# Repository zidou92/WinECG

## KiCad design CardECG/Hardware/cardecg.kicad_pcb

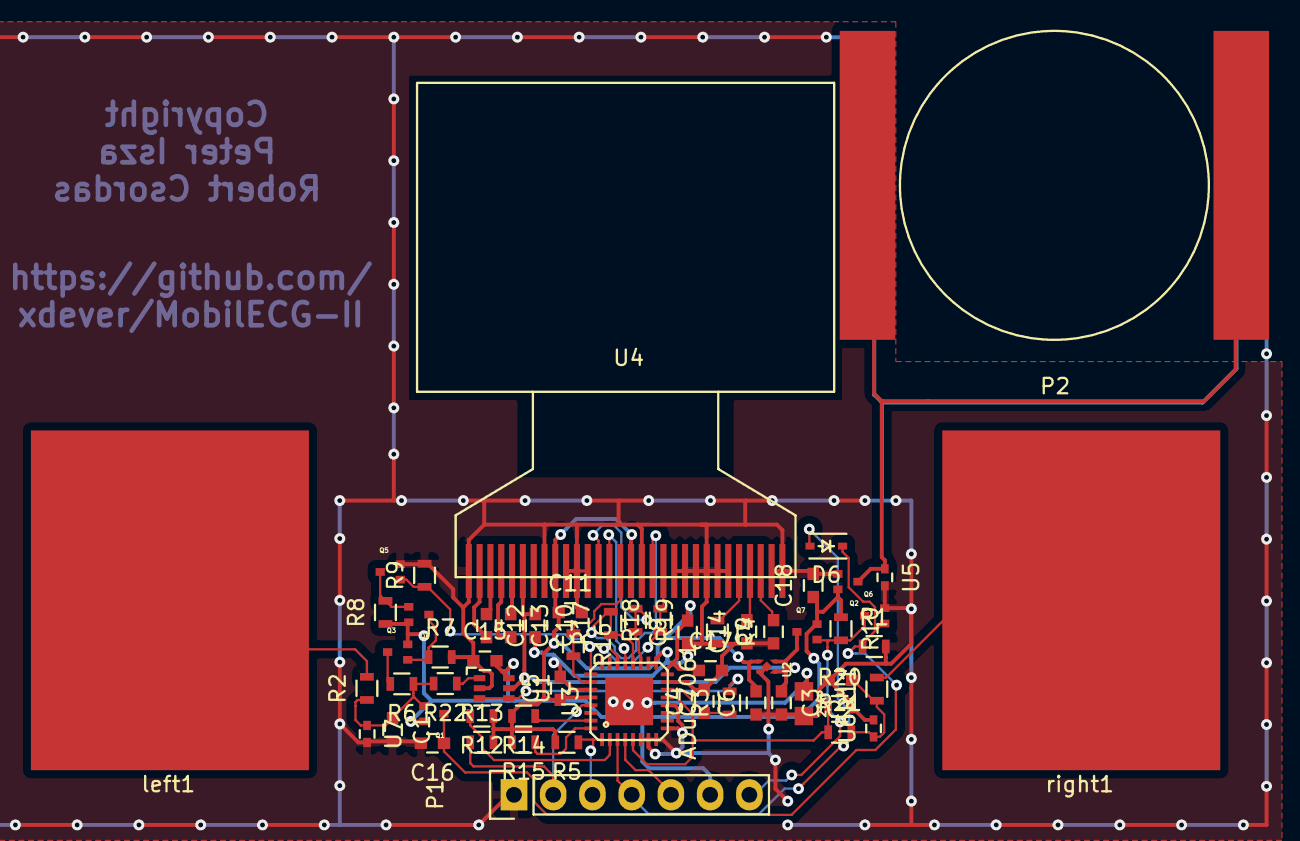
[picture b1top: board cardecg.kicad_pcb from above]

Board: 2 copper layers, 59 parts (0 on the bottom side), 39 nets.

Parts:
C1: 100pF; C_0603
C2, C5, C8, C15, C16: 100nF; C_0603
C3, C6, C10, C11, C12, C13, C17, C18: 1uF; C_0603
C4: 8.2nF NP0; C_0603
C9: 2.2uF; C_0603
C14: 4.7uF 16V; C_0603
CN1: 2TAP
D6: D; SOD-323
P1: PROG; Pin_Header_Straight_1x07
P2: BATTERY; CR2016
Q1, Q2, Q3, Q4, Q7: NX3008PBKT; SOT416
Q5, Q6: NX3008NBKT; SOT416
R1, R2, R3, R5, R8, R9, R10, R11, R12, R14, R15, R20: 47k; R_0603
R4: 390k; R_0603
R6, R7: 10M; R_0603
R13, R21, R22: 3.9k; R_0603
R16, R17, R18, R19: 49; R_0603
U1: LMV341; SC-70-6
U2: LD6805K/25; DFN1010C-4
U3: ADuC7061; LFCSP_VQ_CP32-2
U4: SSD1306
U5, U6, U7: TPD1E10B06; C_0402
left1: CONN_1; ecgpad
right1: CONN_1; ecgpad

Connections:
+BATT: C15.2, C18.1, P1.6, Q1.2, Q2.2, Q3.2, Q4.2, Q7.2, R8.1, R10.1, U1.6
GND: C1.2, C2.2, C3.2, C4.2, C5.2, C6.1, C8.1, C9.1, C10.2, C11.2, C14.1, C15.1, C16.2, C17.2, C18.2, CN1.2, P1.1, P2.3, P2.4, Q2.1, Q5.2, Q6.2, R1.2, R4.2, R7.2, R9.2, R20.2, U1.2, U2.2, U2.PAD, U3.6, U3.7, U3.8, U3.9, U3.12, U3.15, U3.17, U3.18, U3.27, U4.1, U4.8, U4.10, U4.11, U4.12, U4.17, U4.20, U4.21, U4.22, U4.23, U4.24, U4.25, U4.29, U4.30, U5.2, U6.2, U7.2
unnamed: C1.1, Q1.1, R2.1, R6.1, R22.2, U7.1
unnamed: C2.1, R11.1, R21.2, U6.1
unnamed: C4.1, R3.1, U3.14
unnamed: C9.2, U4.28
unnamed: C12.1, U4.3
unnamed: C12.2, U4.2
unnamed: C13.1, U4.5
unnamed: C13.2, U4.4
unnamed: C14.2, U4.27
unnamed: C16.1, D6.1, Q1.3, Q6.1, R1.1
unnamed: CN1.1, U3.33
unnamed: P2.1, P2.2, Q2.3, U5.1
unnamed: Q3.1, Q4.3, R7.1
unnamed: Q3.3, R6.2
unnamed: Q4.1, Q5.3, R8.2
unnamed: R2.2, left1.1
unnamed: R3.2, U1.3, U1.4
unnamed: R4.1, U4.26
unnamed: R11.2, right1.1
unnamed: R12.2, U3.2
unnamed: R14.1, U3.31
unnamed: R15.1, U3.32
unnamed: R16.1, R16.2, U3.26, U4.15
unnamed: R17.1, R17.2, U3.20, U4.18
unnamed: R18.1, R18.2, U3.22, U4.19
unnamed: R19.1, R19.2, U3.19, U4.13
unnamed: R20.1, R21.1, U3.5, U3.13
unnamed: R22.1, U1.1
unnamed: U3.21, U4.14
PULLUP_OFF: Q5.1, R9.1, U3.25
RX/POWER_ON: D6.2, P1.4, U3.3
TX: P1.5, U3.4
VCC: C3.1, C10.1, Q7.3, U1.5, U2.3, U2.4, U4.6
VDD: C5.1, C6.2, C8.2, C11.1, C17.1, R5.2, R12.1, R13.2, R14.2, R15.2, U2.1, U3.16, U3.28, U4.9, U4.16
~FORCE_ON: P1.7, Q6.3, Q7.1, R10.2
~PROG: P1.2, R13.1, U3.29
~RESET: P1.3, R5.1, U3.1

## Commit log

2016-02-26 Change TPS717 to TPS71725.
2016-03-01 Battery holder improvements.
2016-03-01 Naming convention fix (issue: "reserved identifier violation #1").
2016-03-03 CardECG PCB fixes.
2016-03-03 Bigger display cutout.
2016-03-05 Fix LDO footprint. Modify makefile for FTDI UART.
2016-03-05 Resistor value fixes/optimizations. EMC resistors on display.
2016-03-06 EMC optimizations. Compoments rearranged to leave more space for the upper PCB.
2016-03-16 Put card into programming mode automatically.
2016-03-16 Change transistors to smaller package.
2016-03-16 Add filter cap, pulldown resistor, battery ESD protection.
2016-03-16 New LDO. Change display to 4 bit SPI. Remove unnecessary transistor and resistor.
2016-03-27 Random modifications.
2016-03-28 Thin opamp and diode
2016-09-04 A bit more specific value for D6
2017-03-29 Firmware ported to new hardware and GCC 6.
2021-11-10 Update README.md
    https://forum.kicad.info/t/warning-avoid-all-links-to-kicad-pcb-org-use-kicad-org/31521
